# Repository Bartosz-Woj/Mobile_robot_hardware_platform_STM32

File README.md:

# Mobile robot hardware platform

## Project Description

**Universal PCB** with STM32G431 with two 2 h-bridges and input/output connectors designed for usage as mobile robot mainboard. The PCB can be use as mainboard for mini sumo robot, balancing robot, linefollower and other similar projects.

## Main functionality

- high range of power suply voltage (recommended: 9-12V PSU or 2S-3S Li-Po)
- STM32G431
- IR receiver
- power lines: 3V3, 5V, 6V5 with step-down converters.
- switch for enabling/disabling power lines
- 2x i2C connector
- 2x servo connector
- 2x encoder connector
- 2x H-bridge (3.6A each)
- 2x 10pin IDC connector
- 1x 16pin IDC connector [for IR distance sensor](https://github.com/Bartosz-Woj/Modulated_infrared_distance_sensor)
- connector for IR sumo [robot start module](https://p1r.se/startmodule/)

## Program uploading and debugging

The ST-link can be connected to the J2 connector by IDC wire to [ST-Link Nucleo board programming shield] (https://github.com/Bartosz-Woj/ST_LINK-Nucleo-programming-shield) or to the connector J6 by goldpin wires.

## Software

In the folder /software there are example projects made in STM32CubeIDE which can be used for hardware testing and for initial configuration:

- initial_configuration - project with initial configuration of CubeMX. In the main function there is code for testing PWM.

## Project status

- electronic desing: finished
- example usage design: on going

## Additional modules

- [ST-Link Nucleo board programming shield](https://github.com/Bartosz-Woj/ST_LINK-Nucleo-programming-shield)
- [Modulated infrared distance sensor module which peak detection](https://github.com/Bartosz-Woj/Modulated_infrared_distance_sensor)

## Usage in mobile robot projects

- [Low cost mini sumo robot](https://github.com/Bartosz-Woj/Mini-sumo-robot)

## Photos

- **Schematic:**  
  
- **PCB top side:**  
  
- **PCB bottom side:**  

- **Debuging mode:**  

- **Example connection with motors**  

---

## Author

- **Project by:** Bartosz-Woj (Bartosz Wojciechowski)
- **Date:** 10.11.2025

---

## License

Licensed under the **CERN Open Hardware License v2 – Permissive (CERN-OHL-P)**  
You are free to **use, modify, and redistribute** this project, provided that you **credit the original author**.

## Changelog

- V1 - initial release
- V2 - minor improvments: modified U3 footprint, rotated J7, updated routing (microcontroller, power section)

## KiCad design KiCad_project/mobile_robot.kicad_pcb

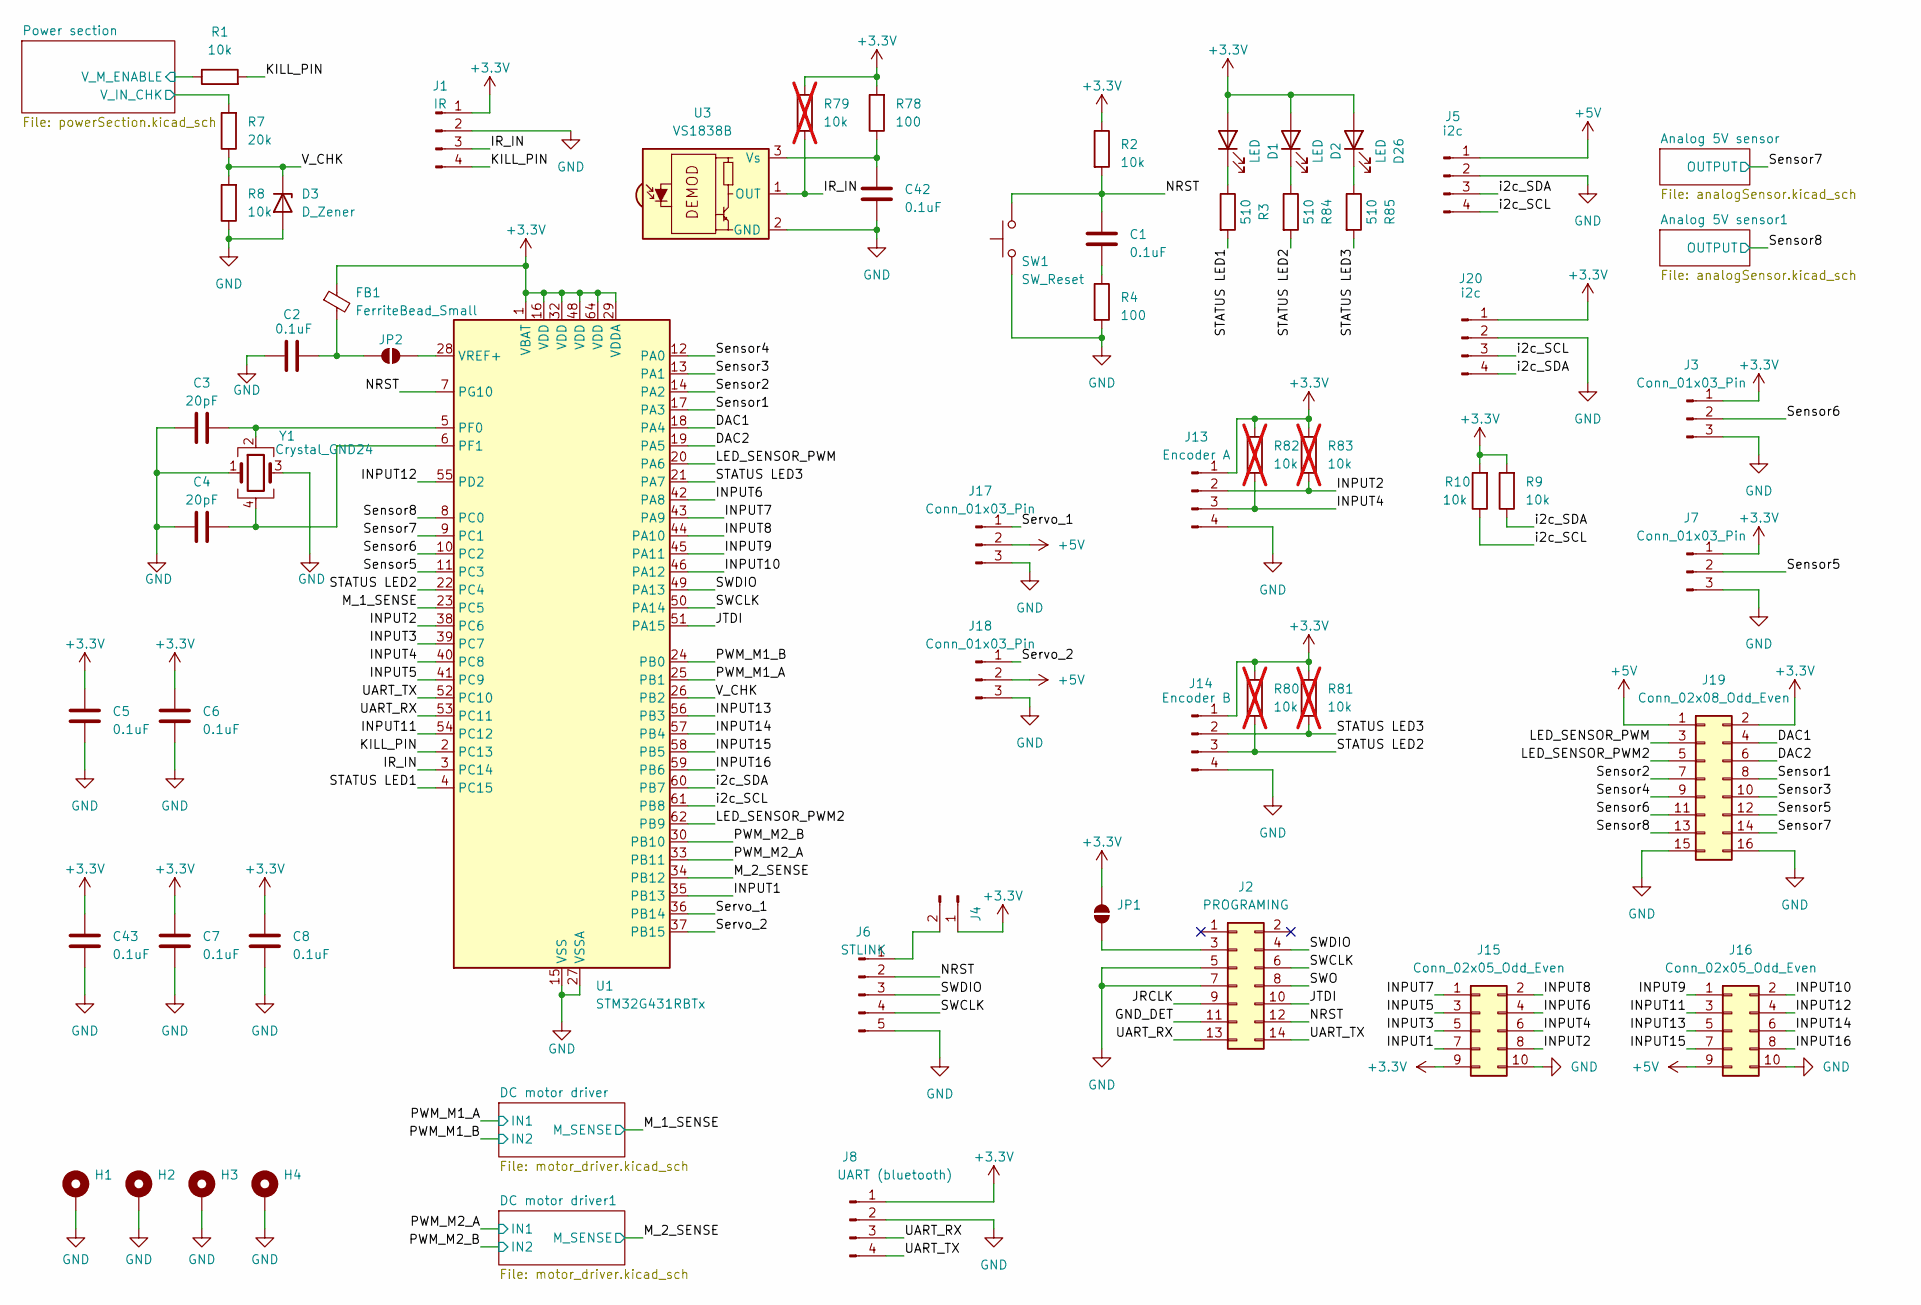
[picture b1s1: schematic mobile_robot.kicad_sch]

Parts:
C1, C42: 0.1uF; C_0805_2012Metric_Pad1.18x1.45mm_HandSolder
C2, C5, C6, C7, C8, C43: 0.1uF; C_0603_1608Metric_Pad1.08x0.95mm_HandSolder
C3, C4: 20pF; C_0805_2012Metric_Pad1.18x1.45mm_HandSolder
D1, D2, D26: LED; LED_0603_1608Metric_Pad1.05x0.95mm_HandSolder
D3: D_Zener; D_MiniMELF
FB1: FerriteBead_Small; L_0805_2012Metric
H1, H2, H3, H4: MountingHole_Pad; MountingHole_3.2mm_M3_ISO14580_Pad
J1: IR; PinSocket_1x04_P2.54mm_Vertical
J2: PROGRAMING; PinHeader_2x07_P1.27mm_Vertical_SMD
J3, J7, J17, J18: Conn_01x03_Pin; PinHeader_1x03_P2.54mm_Vertical
J4: Conn_01x02_Pin; PinHeader_1x02_P2.54mm_Vertical
J5, J20: i2c; PinSocket_1x04_P2.54mm_Vertical
J6: STLINK; PinHeader_1x05_P2.54mm_Vertical
J8: UART (bluetooth); PinSocket_1x04_P2.54mm_Vertical
J13: Encoder A; Molex_KK-254_AE-6410-04A_1x04_P2.54mm_Vertical
J14: Encoder B; Molex_KK-254_AE-6410-04A_1x04_P2.54mm_Vertical
J15, J16: Conn_02x05_Odd_Even; IDC-Header_2x05_P2.54mm_Vertical
J19: Conn_02x08_Odd_Even; IDC-Header_2x08_P2.54mm_Vertical
JP1, JP2: SolderJumper_2_Open; SolderJumper-2_P1.3mm_Open_RoundedPad1.0x1.5mm
R1, R8, R9, R10: 10k; R_0603_1608Metric_Pad0.98x0.95mm_HandSolder
R2: 10k; R_0805_2012Metric_Pad1.20x1.40mm_HandSolder
R3, R84, R85: 510; R_0805_2012Metric_Pad1.20x1.40mm_HandSolder
R4: 100; R_0805_2012Metric_Pad1.20x1.40mm_HandSolder
R7: 20k; R_0603_1608Metric_Pad0.98x0.95mm_HandSolder
R78: 100; R_1206_3216Metric_Pad1.30x1.75mm_HandSolder
R79, R80, R81, R82, R83: 10k; R_0603_1608Metric_Pad0.98x0.95mm_HandSolder; not fitted
SW1: SW_Reset; SW_PUSH_6mm
U1: STM32G431RBTx; LQFP-64_10x10mm_P0.5mm
U3: VS1838B; Vishay_MOLD-3Pin
Y1: Crystal_GND24; Crystal_SMD_3225-4Pin_3.2x2.5mm_HandSoldering

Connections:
+3.3V: C5.1, C6.1, C7.1, C8.1, C43.1, D1.2 (A), D2.2 (A), D26.2 (A), FB1.1, J1.1, J3.1, J4.1, J7.1, J8.1, J13.1, J14.1, J15.9, J19.2, J20.1, JP1.2 (B), R2.1, R9.2, R10.2, R78.2, R79.2, R80.1, R81.1, R82.1, R83.1, U1.1 (VBAT), U1.16 (VDD), U1.29 (VDDA), U1.32 (VDD), U1.48 (VDD), U1.64 (VDD); also elsewhere on the board
+5V: J5.1, J16.9, J17.2, J18.2, J19.1; also elsewhere on the board
/DAC1: J19.4, U1.18 (PA4)
/DAC2: J19.6, U1.19 (PA5)
/GND_DET: J2.11
/INPUT1: J15.7, U1.35 (PB13)
/INPUT2: J13.2, J15.8, R83.2, U1.38 (PC6)
/INPUT3: J15.5, U1.39 (PC7)
/INPUT4: J13.3, J15.6, R82.2, U1.40 (PC8)
/INPUT5: J15.3, U1.41 (PC9)
/INPUT6: J15.4, U1.42 (PA8)
/INPUT7: J15.1, U1.43 (PA9)
/INPUT8: J15.2, U1.44 (PA10)
/INPUT9: J16.1, U1.45 (PA11)
/INPUT10: J16.2, U1.46 (PA12)
/INPUT11: J16.3, U1.54 (PC12)
/INPUT12: J16.4, U1.55 (PD2)
/INPUT13: J16.5, U1.56 (PB3)
/INPUT14: J16.6, U1.57 (PB4)
/INPUT15: J16.7, U1.58 (PB5)
/INPUT16: J16.8, U1.59 (PB6)
/IR_IN: J1.3, R79.1, U1.3 (PC14), U3.1 (OUT)
/JRCLK: J2.9
/JTDI: J2.10, U1.51 (PA15)
/KILL_PIN: J1.4, R1.2, U1.2 (PC13)
/LED_SENSOR_PWM: J19.3, U1.20 (PA6)
/LED_SENSOR_PWM2: J19.5, U1.62 (PB9)
/M_1_SENSE: U1.23 (PC5); also elsewhere on the board
/M_2_SENSE: U1.34 (PB12); also elsewhere on the board
/NRST: C1.1, J2.12, J6.2, R2.2, SW1.2, U1.7 (PG10)
/PWM_M1_A: U1.25 (PB1); also elsewhere on the board
/PWM_M1_B: U1.24 (PB0); also elsewhere on the board
/PWM_M2_A: U1.33 (PB11); also elsewhere on the board
/PWM_M2_B: U1.30 (PB10); also elsewhere on the board
/Power section/V_IN_CHK: R7.2; also elsewhere on the board
/Power section/V_M_ENABLE: R1.1; also elsewhere on the board
/STATUS LED1: R3.2, U1.4 (PC15)
/STATUS LED2: J14.3, R80.2, R84.2, U1.22 (PC4)
/STATUS LED3: J14.2, R81.2, R85.2, U1.21 (PA7)
/SWCLK: J2.6, J6.4, U1.50 (PA14)
/SWDIO: J2.4, J6.3, U1.49 (PA13)
/SWO: J2.8
/Sensor1: J19.8, U1.17 (PA3)
/Sensor2: J19.7, U1.14 (PA2)
/Sensor3: J19.10, U1.13 (PA1)
/Sensor4: J19.9, U1.12 (PA0)
/Sensor5: J7.2, J19.12, U1.11 (PC3)
/Sensor6: J3.2, J19.11, U1.10 (PC2)
/Sensor7: J19.14, U1.9 (PC1); also elsewhere on the board
/Sensor8: J19.13, U1.8 (PC0); also elsewhere on the board
/Servo_1: J17.1, U1.36 (PB14)
/Servo_2: J18.1, U1.37 (PB15)
/UART_RX: J2.13, J8.3, U1.53 (PC11)
/UART_TX: J2.14, J8.4, U1.52 (PC10)
/V_CHK: D3.1 (K), R7.1, R8.2, U1.26 (PB2)
/i2c_SCL: J5.4, J20.3, R10.1, U1.61 (PB8)
/i2c_SDA: J5.3, J20.4, R9.1, U1.60 (PB7)
GND: C2.1, C3.2, C4.2, C5.2, C6.2, C7.2, C8.2, C42.2, C43.2, D3.2 (A), H1.1, H2.1, H3.1, H4.1, J1.2, J2.5, J2.7, J3.3, J5.2, J6.5, J7.3, J8.2, J13.4, J14.4, J15.10, J16.10, J17.3, J18.3, J19.15, J19.16, J20.2, R4.2, R8.1, SW1.1, U1.15 (VSS), U1.27 (VSSA), U1.31 (VSS), U1.47 (VSS), U1.63 (VSS), U3.2 (GND), Y1.1, Y1.3; also elsewhere on the board
unnamed: C1.2, R4.1
unnamed: D1.1 (K), R3.1
unnamed: D2.1 (K), R84.1
unnamed: D26.1 (K), R85.1
unnamed: J2.3, JP1.1 (A)
unnamed: J4.2, J6.1
unnamed: C2.2, FB1.2, JP2.1 (A)
unnamed: JP2.2 (B), U1.28 (VREF+)
unnamed: C3.1, U1.5 (PF0), Y1.2
unnamed: C4.1, U1.6 (PF1), Y1.4
unnamed: C42.1, R78.1, U3.3 (Vs)

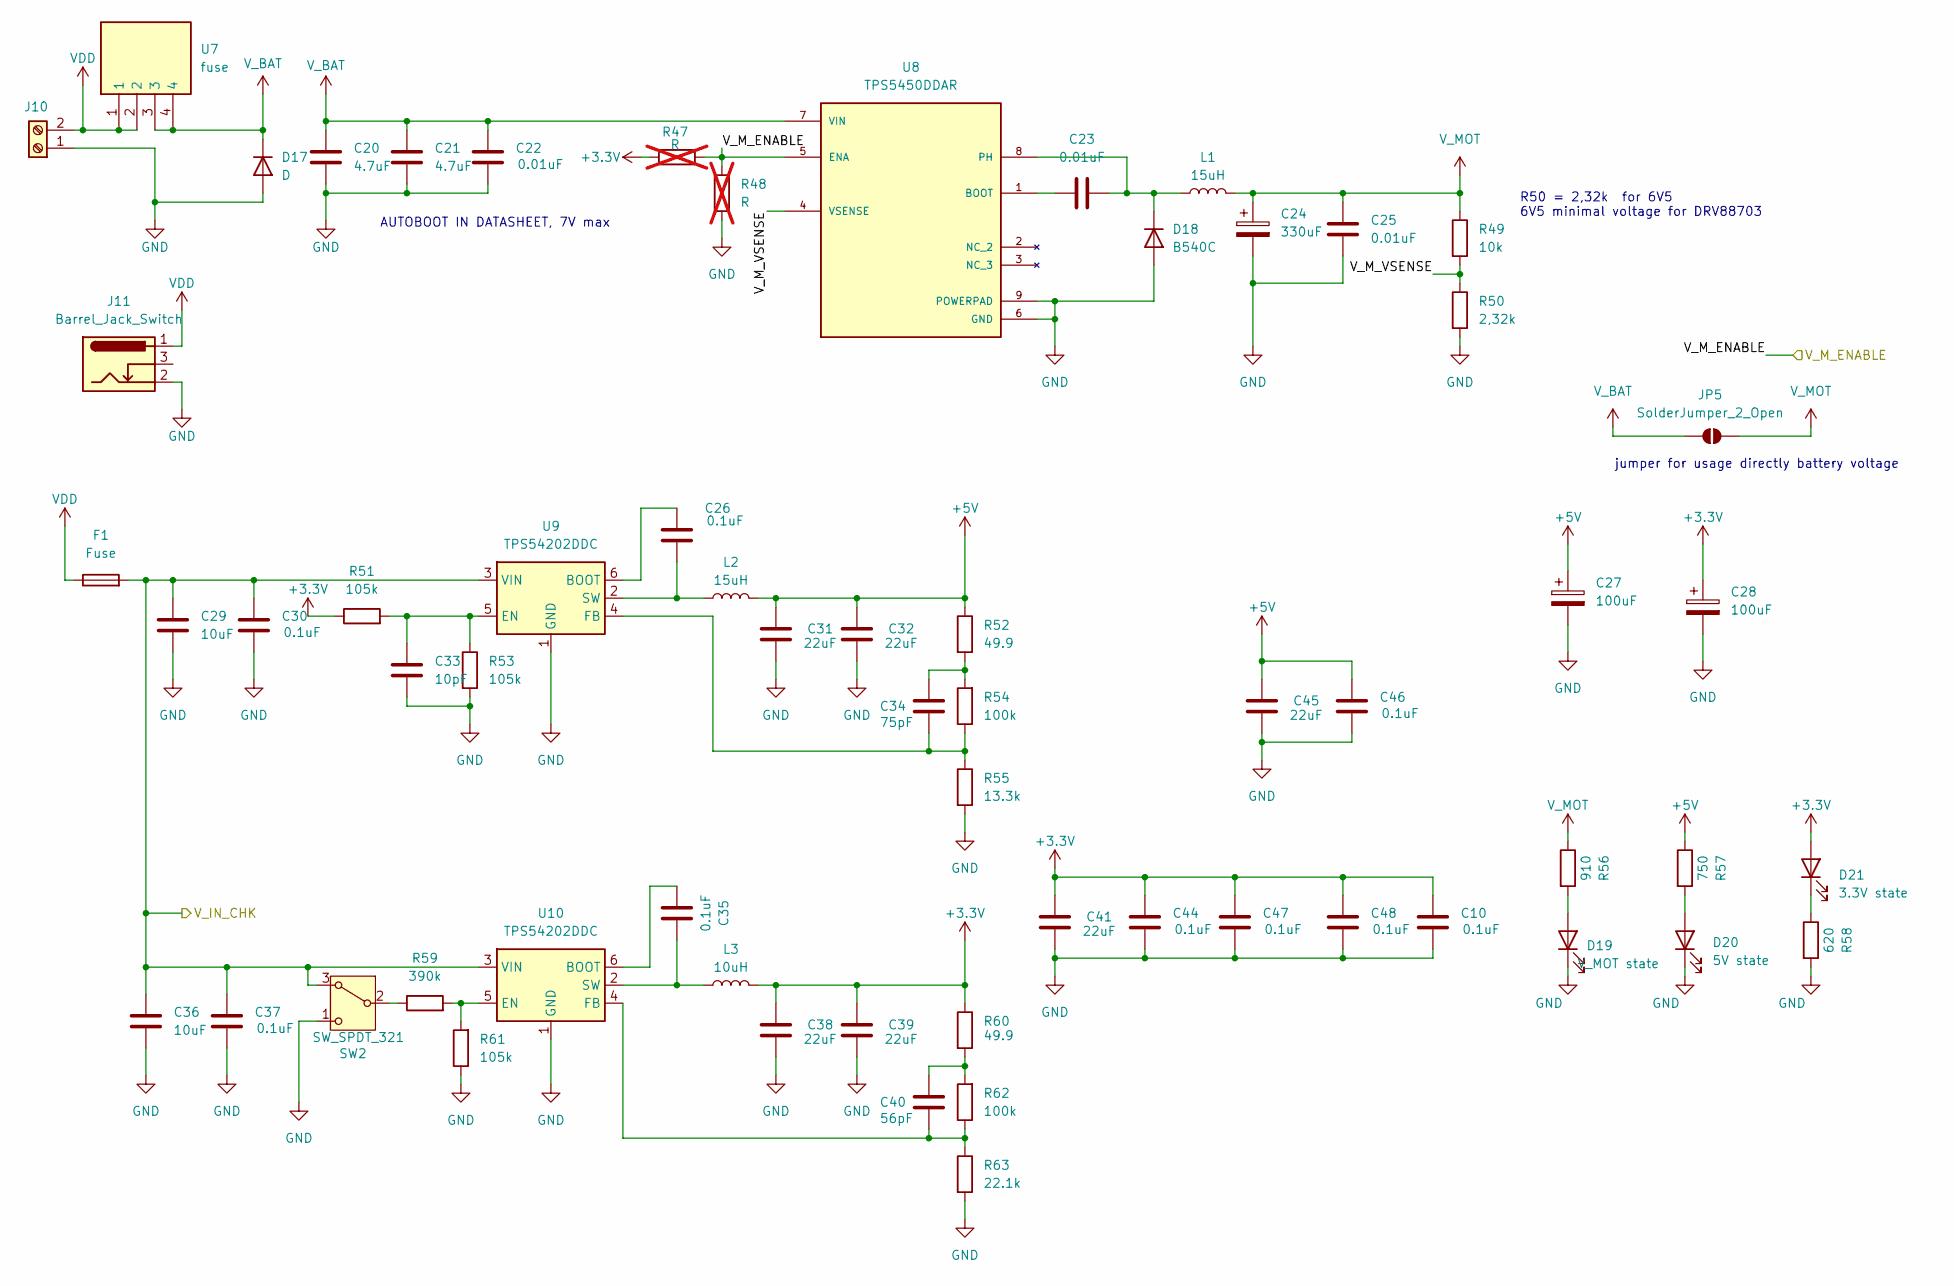
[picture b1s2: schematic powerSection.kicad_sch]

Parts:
C10, C26, C30, C35, C37, C44, C46, C47, C48: 0.1uF; C_0603_1608Metric_Pad1.08x0.95mm_HandSolder
C20, C21: 4.7uF; C_1206_3216Metric_Pad1.33x1.80mm_HandSolder
C22, C23, C25: 0.01uF; C_0603_1608Metric_Pad1.08x0.95mm_HandSolder
C24: 330uF; CP_Elec_8x10.5
C27, C28: 100uF; CP_Elec_8x10.5
C29, C36: 10uF; C_1206_3216Metric_Pad1.33x1.80mm_HandSolder
C31, C32, C38, C39, C41, C45: 22uF; C_1206_3216Metric_Pad1.33x1.80mm_HandSolder
C33: 10pF; C_0603_1608Metric_Pad1.08x0.95mm_HandSolder
C34: 75pF; C_0603_1608Metric_Pad1.08x0.95mm_HandSolder
C40: 56pF; C_0603_1608Metric_Pad1.08x0.95mm_HandSolder
D17: D; D_SMA
D18: B540C; D_SMC
D19: V_MOT state; LED_0603_1608Metric_Pad1.05x0.95mm_HandSolder
D20: 5V state; LED_0603_1608Metric_Pad1.05x0.95mm_HandSolder
D21: 3.3V state; LED_0603_1608Metric_Pad1.05x0.95mm_HandSolder
F1: Fuse; Fuseholder_Littelfuse_Nano2_154x
J10: Screw_Terminal_01x02; TerminalBlock_Phoenix_PT-1,5-2-5.0-H_1x02_P5.00mm_Horizontal
J11: Barrel_Jack_Switch; BarrelJack_GCT_DCJ200-10-A_Horizontal
JP5: SolderJumper_2_Open; SolderJumper-2_P1.3mm_Open_RoundedPad1.0x1.5mm
L1, L2: 15uH; L_TechFuse_SL1040
L3: 10uH; L_TechFuse_SL1040
R47, R48: R; R_0603_1608Metric_Pad0.98x0.95mm_HandSolder; not fitted
R49: 10k; R_0603_1608Metric_Pad0.98x0.95mm_HandSolder
R50: 2,32k; R_0603_1608Metric_Pad0.98x0.95mm_HandSolder
R51, R53, R61: 105k; R_0603_1608Metric_Pad0.98x0.95mm_HandSolder
R52, R60: 49.9; R_0603_1608Metric_Pad0.98x0.95mm_HandSolder
R54, R62: 100k; R_0603_1608Metric_Pad0.98x0.95mm_HandSolder
R55: 13.3k; R_0603_1608Metric_Pad0.98x0.95mm_HandSolder
R56: 910; R_0805_2012Metric_Pad1.20x1.40mm_HandSolder
R57: 750; R_0805_2012Metric_Pad1.20x1.40mm_HandSolder
R58: 620; R_0805_2012Metric_Pad1.20x1.40mm_HandSolder
R59: 390k; R_0603_1608Metric_Pad0.98x0.95mm_HandSolder
R63: 22.1k; R_0603_1608Metric_Pad0.98x0.95mm_HandSolder
SW2: SW_SPDT_321; SW_Slide_SPDT_Angled_CK_OS102011MA1Q
U7: fuse; 01000063Zfuse; Manufacturer_Part_Number 01000063Z; Mouser Part Number 576-01000063Z
U8: TPS5450DDAR; CONV_TPS5450DDAR; PARTREV D
U9, U10: TPS54202DDC; SOT-23-6

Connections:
+3.3V: C10.1, C28.1, C38.1, C39.1, C41.1, C44.1, C47.1, C48.1, D21.2 (A), L3.2, R47.1, R51.1, R60.1; also elsewhere on the board
+5V: C27.1, C31.1, C32.1, C45.1, C46.1, L2.2, R52.1, R57.1; also elsewhere on the board
/Power section/V_IN_CHK: C29.1, C30.1, C36.1, C37.1, F1.2, SW2.3 (A), U9.3 (VIN), U10.3 (VIN); also elsewhere on the board
/Power section/V_M_ENABLE: R47.2, R48.2, U8.5 (ENA); also elsewhere on the board
/Power section/V_M_VSENSE: R49.2, R50.1, U8.4 (VSENSE)
GND: C10.2, C20.2, C21.2, C22.2, C24.2, C25.2, C27.2, C28.2, C29.2, C30.2, C31.2, C32.2, C33.2, C36.2, C37.2, C38.2, C39.2, C41.2, C44.2, C45.2, C46.2, C47.2, C48.2, D17.2 (A), D18.2 (A), D19.1 (K), D20.1 (K), J10.1, J11.2, R48.1, R50.2, R53.2, R55.2, R58.2, R61.1, R63.2, SW2.1 (C), U8.6 (GND), U8.9 (POWERPAD), U9.1 (GND), U10.1 (GND); also elsewhere on the board
unnamed: C34.2, R52.2, R54.2
unnamed: C40.2, R60.2, R62.2
unnamed: C23.2, D18.1 (K), L1.1, U8.8 (PH)
unnamed: D19.2 (A), R56.2
unnamed: D20.2 (A), R57.2
unnamed: D21.1 (K), R58.1
unnamed: R59.1, SW2.2 (B)
unnamed: C23.1, U8.1 (BOOT)
unnamed: C26.1, U9.6 (BOOT)
unnamed: C33.1, R51.2, R53.1, U9.5 (EN)
unnamed: C34.1, R54.1, R55.1, U9.4 (FB)
unnamed: C26.2, L2.1, U9.2 (SW)
unnamed: C35.1, U10.6 (BOOT)
unnamed: R59.2, R61.2, U10.5 (EN)
unnamed: C40.1, R62.1, R63.1, U10.4 (FB)
unnamed: C35.2, L3.1, U10.2 (SW)
VDD: F1.1, J10.2, J11.1, U7.1, U7.2
V_BAT: C20.1, C21.1, C22.1, D17.1 (K), JP5.1 (A), U7.3, U7.4, U8.7 (VIN)
V_MOT: C24.1, C25.1, JP5.2 (B), L1.2, R49.1, R56.1; also elsewhere on the board

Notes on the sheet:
AUTOBOOT IN DATASHEET, 7V max
jumper for usage directly battery voltage
R50 = 2,32k for 6V5 6V5 minimal voltage for DRV88703

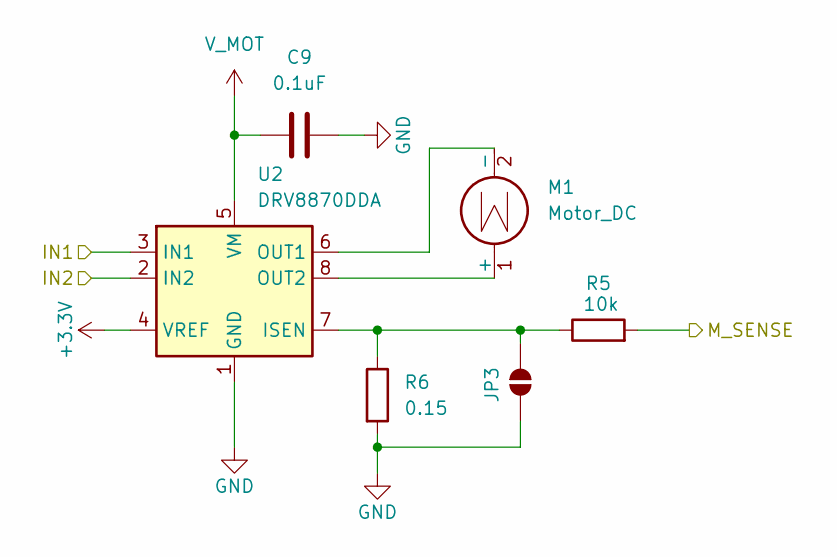
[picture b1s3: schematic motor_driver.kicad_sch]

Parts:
C9: 0.1uF; C_0603_1608Metric_Pad1.08x0.95mm_HandSolder
JP3: SolderJumper_2_Open; SolderJumper-2_P1.3mm_Open_RoundedPad1.0x1.5mm
M1: Motor_DC; TerminalBlock_Phoenix_PT-1,5-2-5.0-H_1x02_P5.00mm_Horizontal
R5: 10k; R_0603_1608Metric_Pad0.98x0.95mm_HandSolder
R6: 0.15; R_2512_6332Metric_Pad1.40x3.35mm_HandSolder
U2: DRV8870DDA; Texas_HTSOP-8-1EP_3.9x4.9mm_P1.27mm_EP2.95x4.9mm_Mask2.4x3.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

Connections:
+3.3V: U2.4 (VREF); also elsewhere on the board
/M_2_SENSE: R5.2; also elsewhere on the board
/PWM_M2_A: U2.3 (IN1); also elsewhere on the board
/PWM_M2_B: U2.2 (IN2); also elsewhere on the board
GND: C9.2, JP3.1 (A), R6.2, U2.1 (GND), U2.9 (GND); also elsewhere on the board
unnamed: JP3.2 (B), R5.1, R6.1, U2.7 (ISEN)
unnamed: M1.1 (+), U2.8 (OUT2)
unnamed: M1.2 (-), U2.6 (OUT1)
V_MOT: C9.1, U2.5 (VM); also elsewhere on the board

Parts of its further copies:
C11: 0.1uF; C_0603_1608Metric_Pad1.08x0.95mm_HandSolder
JP4: SolderJumper_2_Open; SolderJumper-2_P1.3mm_Open_RoundedPad1.0x1.5mm
M2: Motor_DC; TerminalBlock_Phoenix_PT-1,5-2-5.0-H_1x02_P5.00mm_Horizontal
R19: 10k; R_0603_1608Metric_Pad0.98x0.95mm_HandSolder
R20: 0.15; R_2512_6332Metric_Pad1.40x3.35mm_HandSolder
U4: DRV8870DDA; Texas_HTSOP-8-1EP_3.9x4.9mm_P1.27mm_EP2.95x4.9mm_Mask2.4x3.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

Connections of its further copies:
+3.3V: U4.4 (VREF); also elsewhere on the board
/M_1_SENSE: R19.2; also elsewhere on the board
/PWM_M1_A: U4.3 (IN1); also elsewhere on the board
/PWM_M1_B: U4.2 (IN2); also elsewhere on the board
GND: C11.2, JP4.1 (A), R20.2, U4.1 (GND), U4.9 (GND); also elsewhere on the board
unnamed: JP4.2 (B), R19.1, R20.1, U4.7 (ISEN)
unnamed: M2.1 (+), U4.8 (OUT2)
unnamed: M2.2 (-), U4.6 (OUT1)
V_MOT: C11.1, U4.5 (VM); also elsewhere on the board

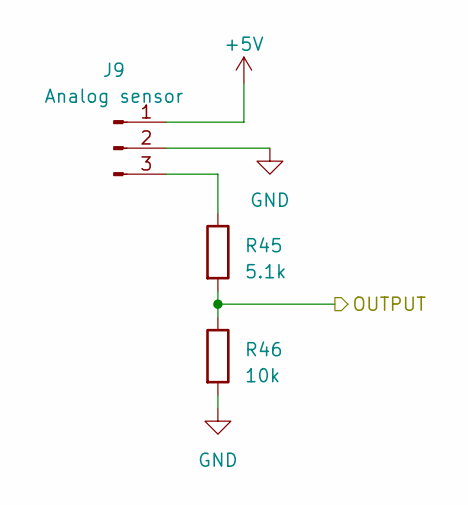
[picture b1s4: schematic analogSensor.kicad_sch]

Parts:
J9: Analog sensor; JST_XH_B3B-XH-A_1x03_P2.50mm_Vertical
R45: 5.1k; R_0603_1608Metric_Pad0.98x0.95mm_HandSolder
R46: 10k; R_0603_1608Metric_Pad0.98x0.95mm_HandSolder

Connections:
+5V: J9.1; also elsewhere on the board
/Sensor7: R45.2, R46.1; also elsewhere on the board
GND: J9.2, R46.2; also elsewhere on the board
unnamed: J9.3, R45.1

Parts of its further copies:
J12: Analog sensor; JST_XH_B3B-XH-A_1x03_P2.50mm_Vertical
R76: 5.1k; R_0603_1608Metric_Pad0.98x0.95mm_HandSolder
R77: 10k; R_0603_1608Metric_Pad0.98x0.95mm_HandSolder

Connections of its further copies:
+5V: J12.1; also elsewhere on the board
/Sensor8: R76.2, R77.1; also elsewhere on the board
GND: J12.2, R77.2; also elsewhere on the board
unnamed: J12.3, R76.1

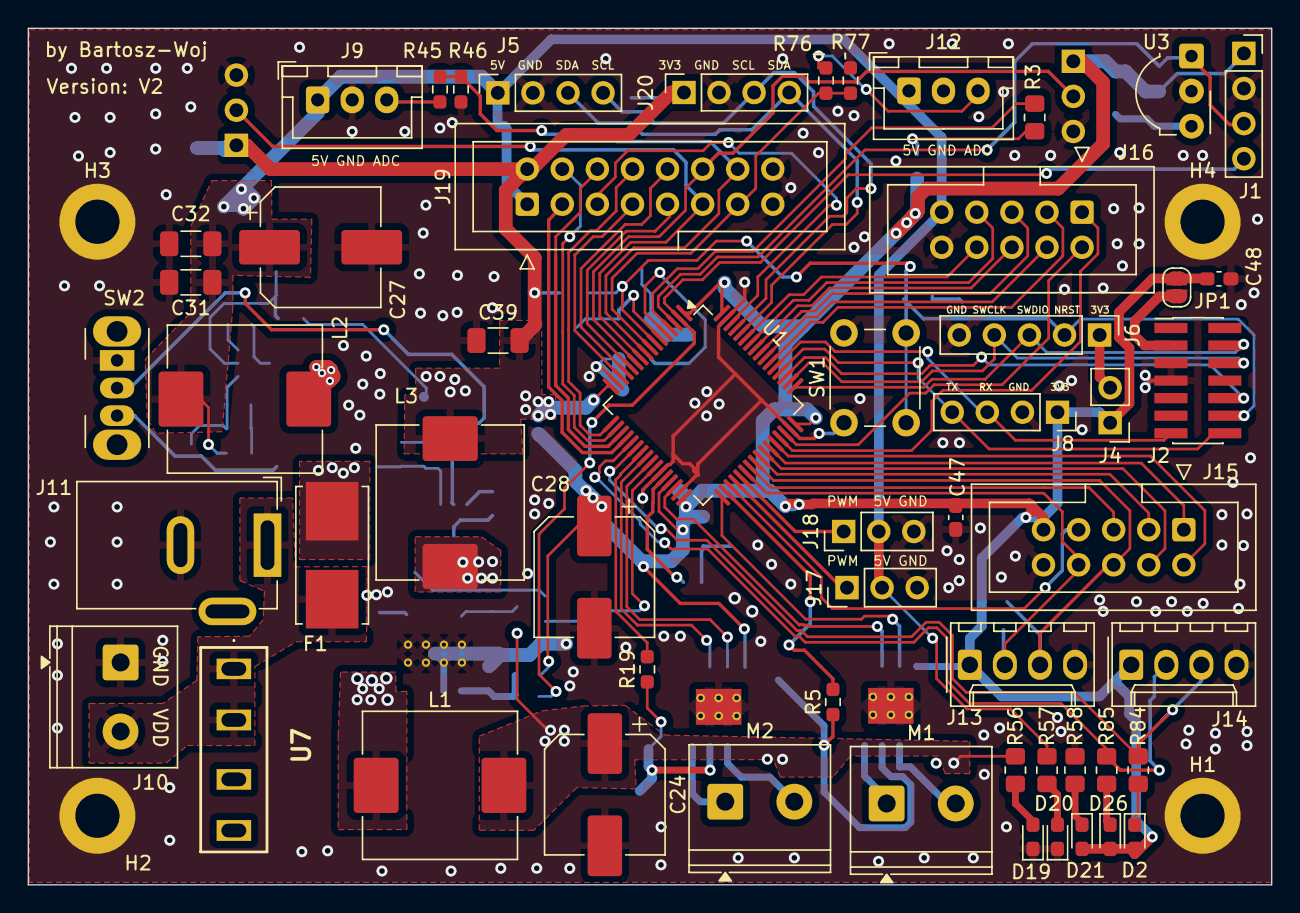
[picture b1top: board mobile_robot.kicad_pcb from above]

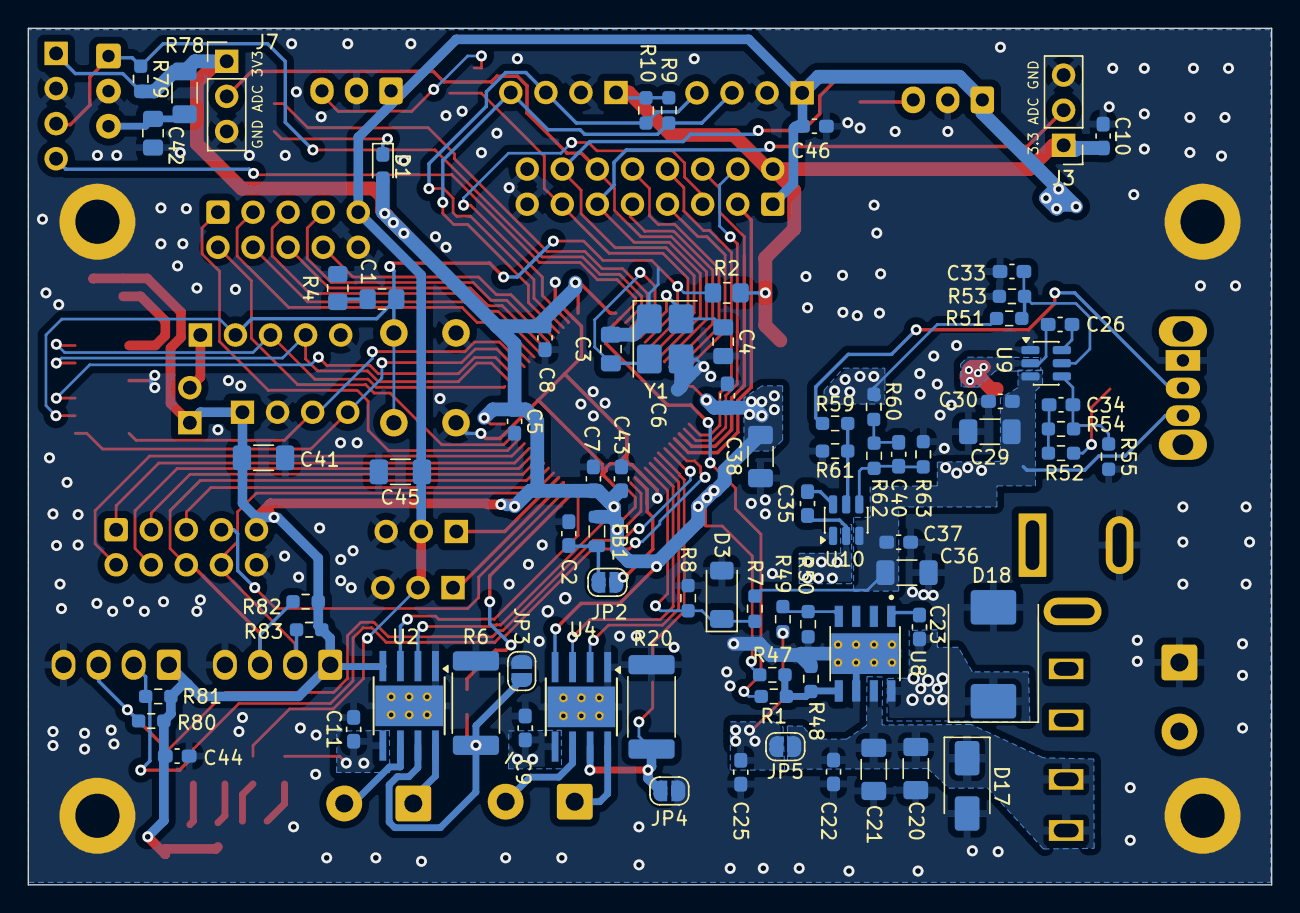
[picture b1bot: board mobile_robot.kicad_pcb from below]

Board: 2 copper layers, 90.0 x 62.0 mm, 137 parts (78 on the bottom side), 94 nets.

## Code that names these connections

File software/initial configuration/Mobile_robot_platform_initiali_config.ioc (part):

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Mcu.Name=STM32G431R(6-8-B)Tx
Mcu.Package=LQFP64
Mcu.UserName=STM32G431RBTx
PA0.Mode=IN1-Single-Ended
PA0.Signal=ADC2_IN1
PA1.Mode=IN2-Single-Ended
PA1.Signal=ADC2_IN2
PA10.Signal=GPIO_Input
PA11.Signal=GPIO_Input
PA12.Signal=GPIO_Input
PA13.Mode=Serial_Wire
PA13.Signal=SYS_JTMS-SWDIO
PA14.Mode=Serial_Wire
PA14.Signal=SYS_JTCK-SWCLK
PA15.Signal=SYS_JTDI
PA2.Mode=IN3-Single-Ended
PA2.Signal=ADC1_IN3
PA3.Signal=ADC1_IN4
PA4.Signal=COMP_DAC11_group
PA5.Signal=COMP_DAC12_group
PA6.GPIOParameters=GPIO_Label
PA6.GPIO_Label=LED_SENSOR_PWM
PA6.Signal=S_TIM16_CH1
PA7.GPIOParameters=GPIO_Label
PA7.GPIO_Label=STATUS_LED3
PA7.Signal=GPIO_Output
PA8.Signal=GPIO_Input
PA9.Signal=GPIO_Input
PB0.Signal=S_TIM3_CH3
PB1.Signal=S_TIM3_CH4
PB10.Signal=S_TIM2_CH3
PB11.Signal=S_TIM2_CH4
PB12.Signal=ADC1_IN11
PB13.Signal=GPIO_Input
PB14.GPIOParameters=GPIO_Label
PB14.GPIO_Label=Servo1
PB14.Signal=S_TIM15_CH1
PB15.GPIOParameters=GPIO_Label
PB15.GPIO_Label=Servo2
PB15.Signal=S_TIM15_CH2
PB2.GPIOParameters=GPIO_Label
PB2.GPIO_Label=V_VHK
PB2.Signal=ADC2_IN12
PB3.Signal=GPIO_Input
PB4.Signal=GPIO_Input
PB5.Signal=GPIO_Input
PB6.Signal=GPIO_Input
PB7.Mode=I2C
PB7.Signal=I2C1_SDA
PB8-BOOT0.Mode=I2C
PB8-BOOT0.Signal=I2C1_SCL
PB9.Signal=S_TIM17_CH1
PC0.Mode=IN6-Single-Ended
PC0.Signal=ADC2_IN6
PC1.Mode=IN7-Single-Ended
PC1.Signal=ADC2_IN7
PC10.Mode=Asynchronous
PC10.Signal=USART3_TX
PC11.Mode=Asynchronous
PC11.Signal=USART3_RX
PC12.Signal=GPIO_Input
PC13.GPIOParameters=GPIO_Label
PC13.GPIO_Label=KILL PIN
PC13.Signal=GPIO_Input
PC14-OSC32_IN.GPIOParameters=GPIO_Label
PC14-OSC32_IN.GPIO_Label=IR
PC14-OSC32_IN.Signal=GPXTI14
PC15-OSC32_OUT.GPIOParameters=GPIO_Label
PC15-OSC32_OUT.GPIO_Label=STATUS_LED1
PC15-OSC32_OUT.Signal=GPIO_Output
PC2.Mode=IN8-Single-Ended
PC2.Signal=ADC2_IN8
PC3.Mode=IN9-Single-Ended
PC3.Signal=ADC2_IN9
PC4.GPIOParameters=GPIO_Label
PC4.GPIO_Label=STATUS_LED2
PC4.Signal=GPIO_Output
PC5.Mode=IN11-Single-Ended
PC5.Signal=ADC2_IN11
PC6.Signal=GPIO_Input
PC7.Signal=GPIO_Input
PC8.Signal=GPIO_Input
PC9.Signal=GPIO_Input
PD2.Signal=GPIO_Input
RCC.HSE_VALUE=8000000
RCC.SYSCLKFreq_VALUE=16000000
board=custom

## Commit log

2025-11-11 initial release
    initial release
2025-11-12 bug solving
    - DRC error solving related with I2C pull-up resistors
    - updating readme
2026-04-27 update routing, changed IR sensor with pinout, rotate right sensor connector (bottom side)
2026-04-28 update GND routing
2026-04-28 update gerber files and STEP file
